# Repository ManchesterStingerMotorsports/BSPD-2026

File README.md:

# BSPD Routing Challenge - Manchester Stinger Motorsports

Welcome to the **BSPD Routing Challenge** for the Manchester Stinger Motorsports Formula Student team.

The aim of this challenge is to compare PCB layout and routing quality across the team using **the same fixed schematic and board constraints**.

You will fork this repository, route the PCB, and submit your solution via GitHub.

---

## Objective

Produce the **best-routed PCB** possible while strictly adhering to the constraints below.

This is a **layout-only challenge** - no schematic edits, no mechanical changes, no shortcuts.

---

## Deadline

**9th of February (23:59)**

---

## How to Enter

1. **Fork this repository**
2. Open the project in **KiCad** 
3. Route the PCB according to the rules below
4. Commit your changes
5. Submit your fork for review

---

## Rules (Read Carefully)

### 1. Schematic - DO NOT CHANGE
- The **schematic must remain completely unchanged**
- No component changes
- No footprint changes
- No net changes

Any schematic modification will result in **disqualification**.

---

### 2. Board Outline & Connectors - FIXED
- **Board dimensions must remain unchanged**
- **Board outline must not be edited**
- **All connectors must stay in their original positions and orientations**
- Do not move connectors even slightly

This ensures all layouts are directly comparable.

---

### 3. What You ARE Allowed to Change
- Component placement (except connectors)
- Track routing
- Via count and placement
- Copper pours / zones
- Layer usage
- Trace widths (within design rules)
- Decoupling capacitor placement (if already present in the schematic)

---

### 4. What You Are NOT Allowed to Do
- Modify the schematic in any way
- Add or remove components
- Change connector positions
- Change board size or shape
- Change footprints

---

## Judging Criteria

Layouts will be judged on:

- Signal integrity
- Routing quality
- Layer usage efficiency
- EMI considerations
- Manufacturability/Solderability
- Overall cleanliness and readability

Bonus points for:
- Thoughtful via usage
- Clear functional grouping
- Good silkscreen labelling (feel free to add cool graphics!!)

---

## Submission Guidelines

- Commit **only PCB layout changes**
- Final submission must build cleanly with **no DRC errors**
- Do not squash or rewrite history after submission
- When you are happy with your submission send me (Jame) a message.

---

## Point of Contact

The point of contact for this challenge is **me** (James Platt).

That said, please **ask questions and discuss openly in the `#st-electronics` Slack channel** wherever possible so everyone benefits.

---

## Notes

This challenge is intended to:
- Improve PCB routing skills across the team
- Encourage discussion around best practice
- Foster healthy competition within the sparky subteams

Best of luck!!

Jame ⚡

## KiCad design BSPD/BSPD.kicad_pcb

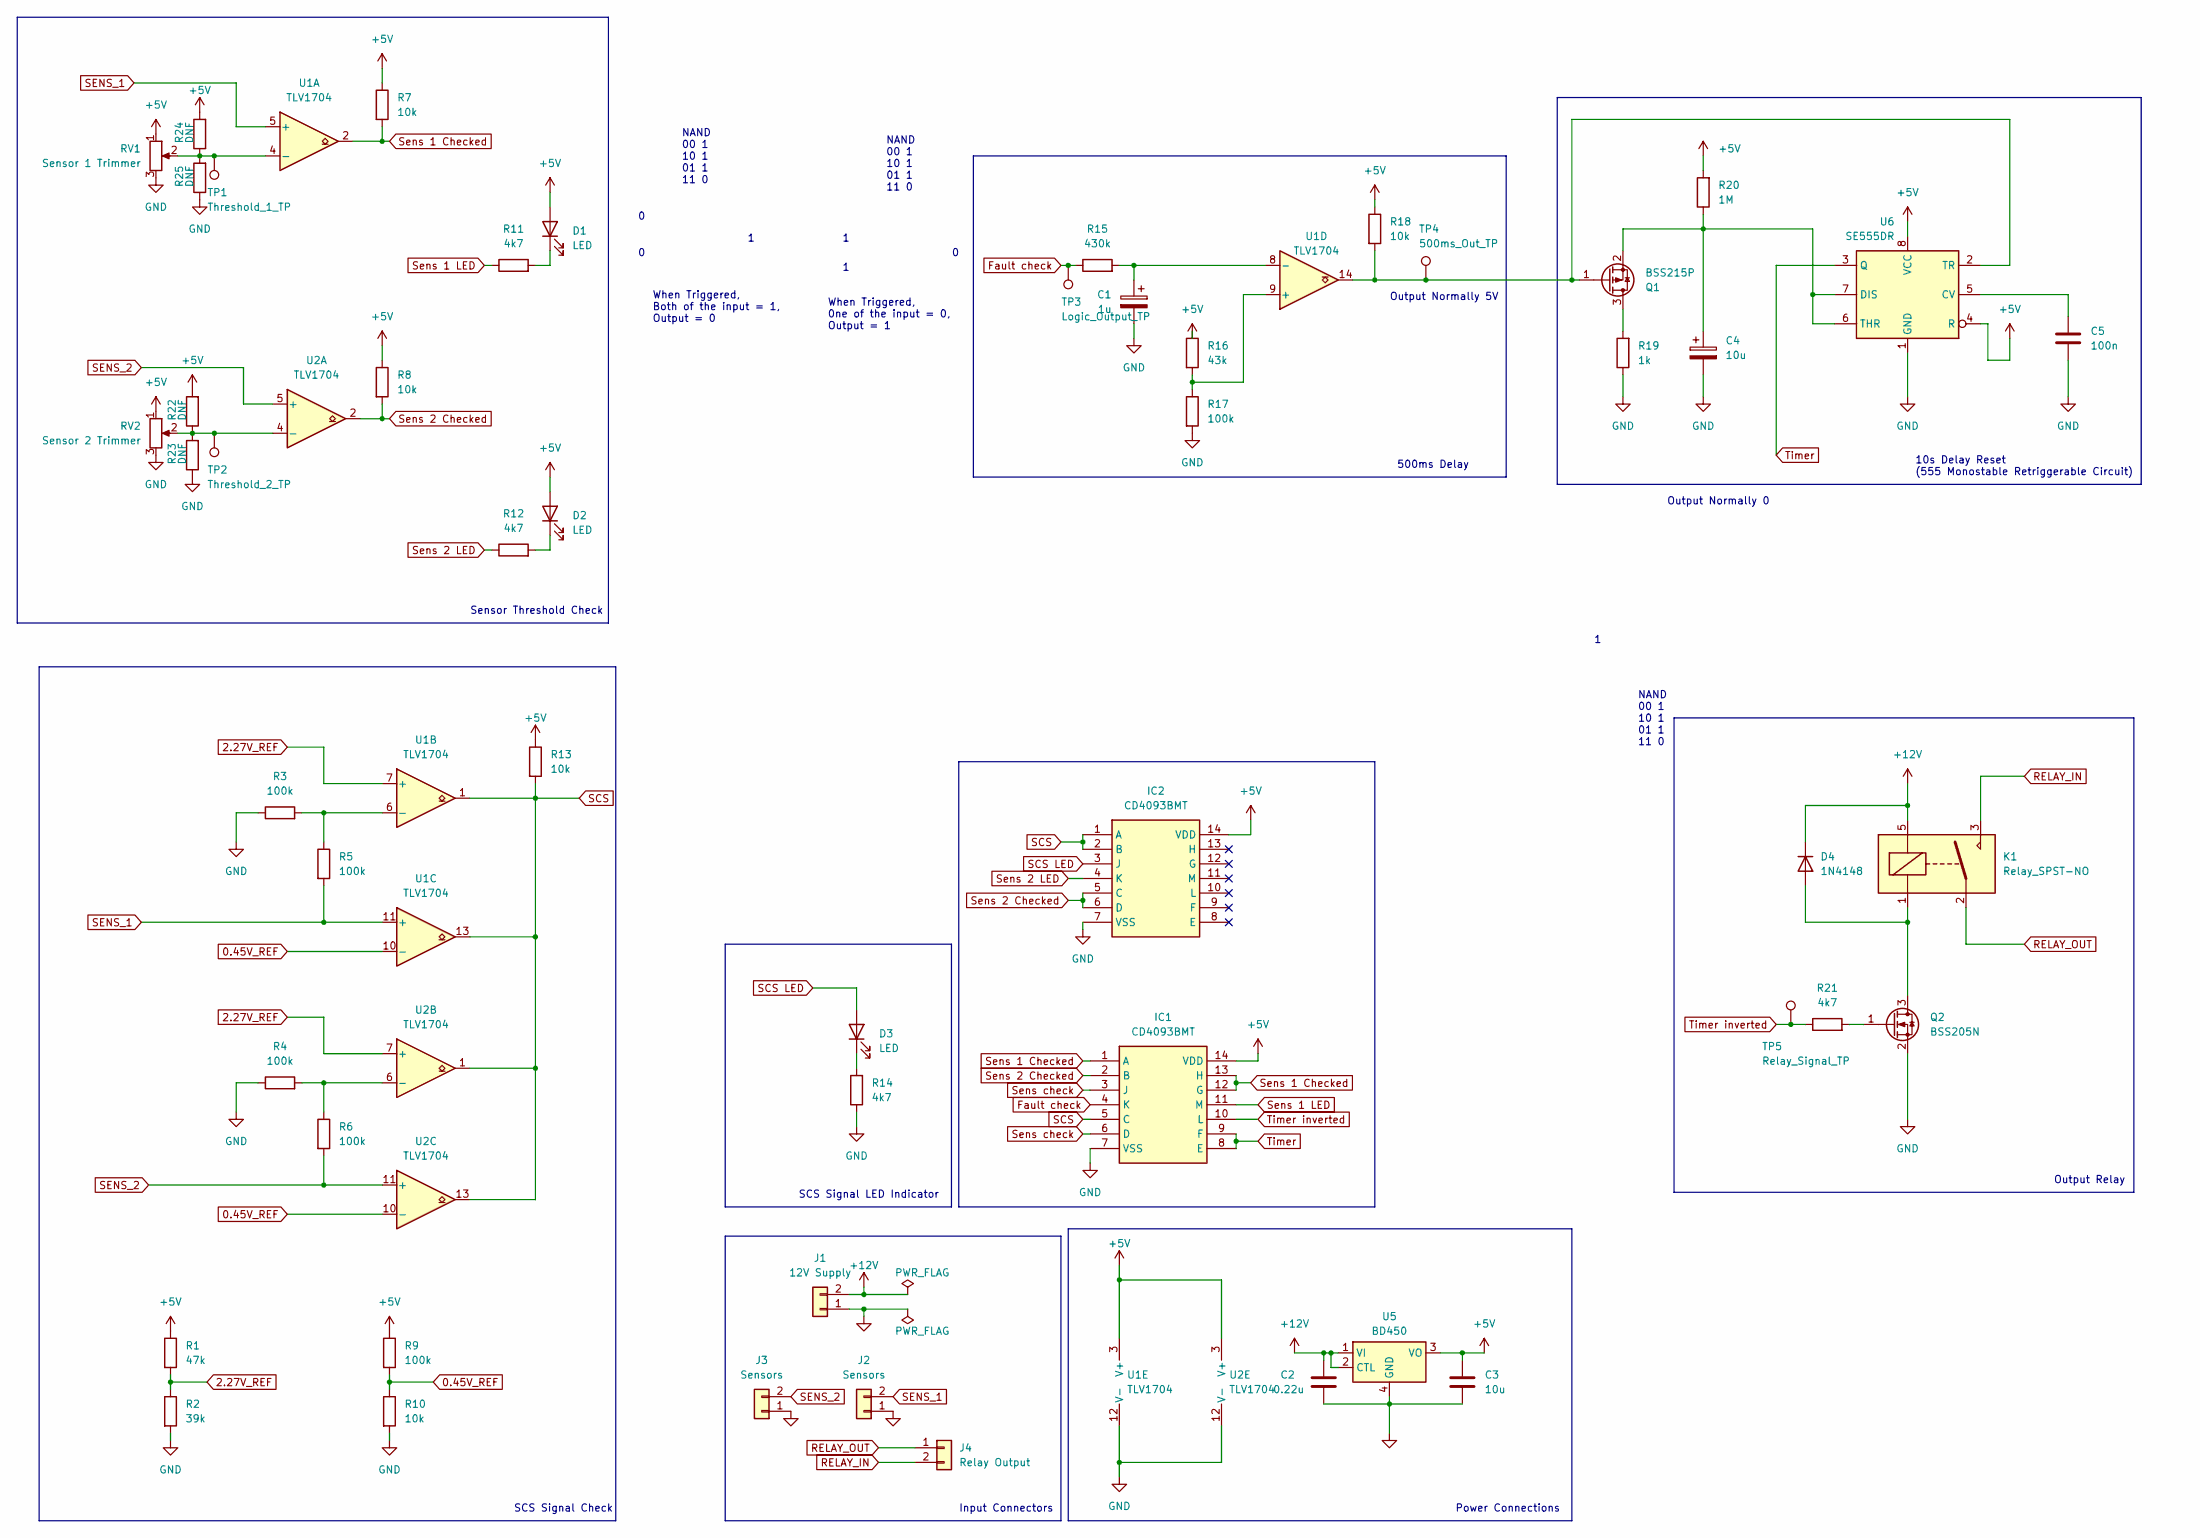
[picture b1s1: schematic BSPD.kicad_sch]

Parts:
C1: 1u; C_0603_1608Metric
C2: 0.22u; C_0603_1608Metric
C3, C4: 10u; C_0603_1608Metric
C5: 100n; C_0603_1608Metric
D1, D2, D3: LED; LED_0603_1608Metric
D4: 1N4148; SOD-123_VISHAY
IC1, IC2: CD4093BMT; Cd4093b; Manufacturer_Part_Number CD4093BMT; Mouser Part Number 595-CD4093BMT
J1: 12V Supply; JST_XA_S02B-XASK-1_1x02_P2.50mm_Horizontal
J2, J3: Sensors; JST_XA_S02B-XASK-1_1x02_P2.50mm_Horizontal
J4: Relay Output; JST_XA_S02B-XASK-1_1x02_P2.50mm_Horizontal
K1: Relay_SPST-NO; RELAY_G6RN-1_OMR
Q1: BSS215P; MOSFET_Single_SOT-23
Q2: BSS205N; MOSFET_Single_SOT-23
R1: 47k; R_0603_1608Metric
R2: 39k; R_0603_1608Metric
R3, R4, R5, R6, R9, R17: 100k; R_0603_1608Metric
R7, R8, R10, R13, R18: 10k; R_0603_1608Metric
R11, R12, R14, R21: 4k7; R_0603_1608Metric
R15: 430k; R_0603_1608Metric
R16: 43k; R_0603_1608Metric
R19: 1k; R_0603_1608Metric
R20: 1M; R_0603_1608Metric
R22, R23, R24, R25: DNF; R_0603_1608Metric
RV1: Sensor 1 Trimmer; Bourns_3314G-1
RV2: Sensor 2 Trimmer; Bourns_3314G-1
TP1: Threshold_1_TP; TestPoint_Pad_2.0x2.0mm
TP2: Threshold_2_TP; TestPoint_Pad_2.0x2.0mm
TP3: Logic_Output_TP; TestPoint_Pad_2.0x2.0mm
TP4: 500ms_Out_TP; TestPoint_Pad_2.0x2.0mm
TP5: Relay_Signal_TP; TestPoint_Pad_2.0x2.0mm
U1, U2: TLV1704; PW14_TEX
U5: BD450; Regulator_Linear_SOT-223-4
U6: SE555DR; D8

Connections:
0.45V_REF: R9.2, R10.1, U1.10 (-), U2.10 (-)
2.27V_REF: R1.2, R2.1, U1.7 (+), U2.7 (+)
+5V: C3.1, D1.2 (A), D2.2 (A), IC1.14 (VDD), IC2.14 (VDD), R1.1, R7.1, R8.1, R9.1, R13.1, R16.1, R18.1, R20.2, R22.2, R24.2, RV1.1, RV2.1, U1.3 (V+), U2.3 (V+), U5.3 (VO), U6.4 (R), U6.8 (VCC)
+12V: C2.1, D4.1 (K), J1.2, K1.5, U5.1 (VI), U5.2 (CTL)
Fault check: IC1.4 (K), R15.1, TP3.1 (1_1)
GND: C1.2, C2.2, C3.2, C4.2, C5.2, IC1.7 (VSS), IC2.7 (VSS), J1.1, J2.1, J3.1, Q2.2 (S), R2.2, R3.1, R4.1, R10.2, R14.1, R17.2, R19.1, R23.1, R25.1, RV1.3, RV2.3, U1.12 (V-), U2.12 (V-), U5.4 (GND), U6.1 (GND)
unnamed: D1.1 (K), R11.2
unnamed: D2.1 (K), R12.2
unnamed: D3.1 (K), R14.2
unnamed: D4.2 (A), K1.1, Q2.3 (D)
unnamed: Q1.3 (D), R19.2
unnamed: Q1.1 (G), R18.2, TP4.1 (1_1), U1.14, U6.2 (TR)
unnamed: C4.1, Q1.2 (S), R20.1, U6.6 (THR), U6.7 (DIS)
unnamed: Q2.1 (G), R21.2
unnamed: R24.1, R25.2, RV1.2, TP1.1 (1_1), U1.4 (-)
unnamed: R3.2, R5.1, U1.6 (-)
unnamed: R16.2, R17.1, U1.9 (+)
unnamed: C1.1, R15.2, U1.8 (-)
unnamed: R22.1, R23.2, RV2.2, TP2.1 (1_1), U2.4 (-)
unnamed: R4.2, R6.1, U2.6 (-)
unnamed: C5.1, U6.5 (CV)
RELAY_IN: J4.2, K1.3
RELAY_OUT: J4.1, K1.2
SCS: IC1.5 (C), IC2.1 (A), IC2.2 (B), R13.2, U1.1, U1.13, U2.1, U2.13
SCS LED: D3.2 (A), IC2.3 (J)
SENS_1: J2.2, R5.2, U1.5 (+), U1.11 (+)
SENS_2: J3.2, R6.2, U2.5 (+), U2.11 (+)
Sens 1 Checked: IC1.1 (A), IC1.12 (G), IC1.13 (H), R7.2, U1.2
Sens 1 LED: IC1.11 (M), R11.1
Sens 2 Checked: IC1.2 (B), IC2.5 (C), IC2.6 (D), R8.2, U2.2
Sens 2 LED: IC2.4 (K), R12.1
Sens check: IC1.3 (J), IC1.6 (D)
Timer: IC1.8 (E), IC1.9 (F), U6.3 (Q)
Timer inverted: IC1.10 (L), R21.1, TP5.1 (1_1)

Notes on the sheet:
SCS Signal Check
When Triggered, Both of the input = 1, Output = 0
500ms Delay
Output Relay
SCS Signal LED Indicator
Power Connections
NAND 00 1 10 1 01 1 11 0
Sensor Threshold Check
Output Normally 5V
Input Connectors
When Triggered, 0ne of the input = 0, Output = 1
10s Delay Reset (555 Monostable Retriggerable Circuit)
Output Normally 0

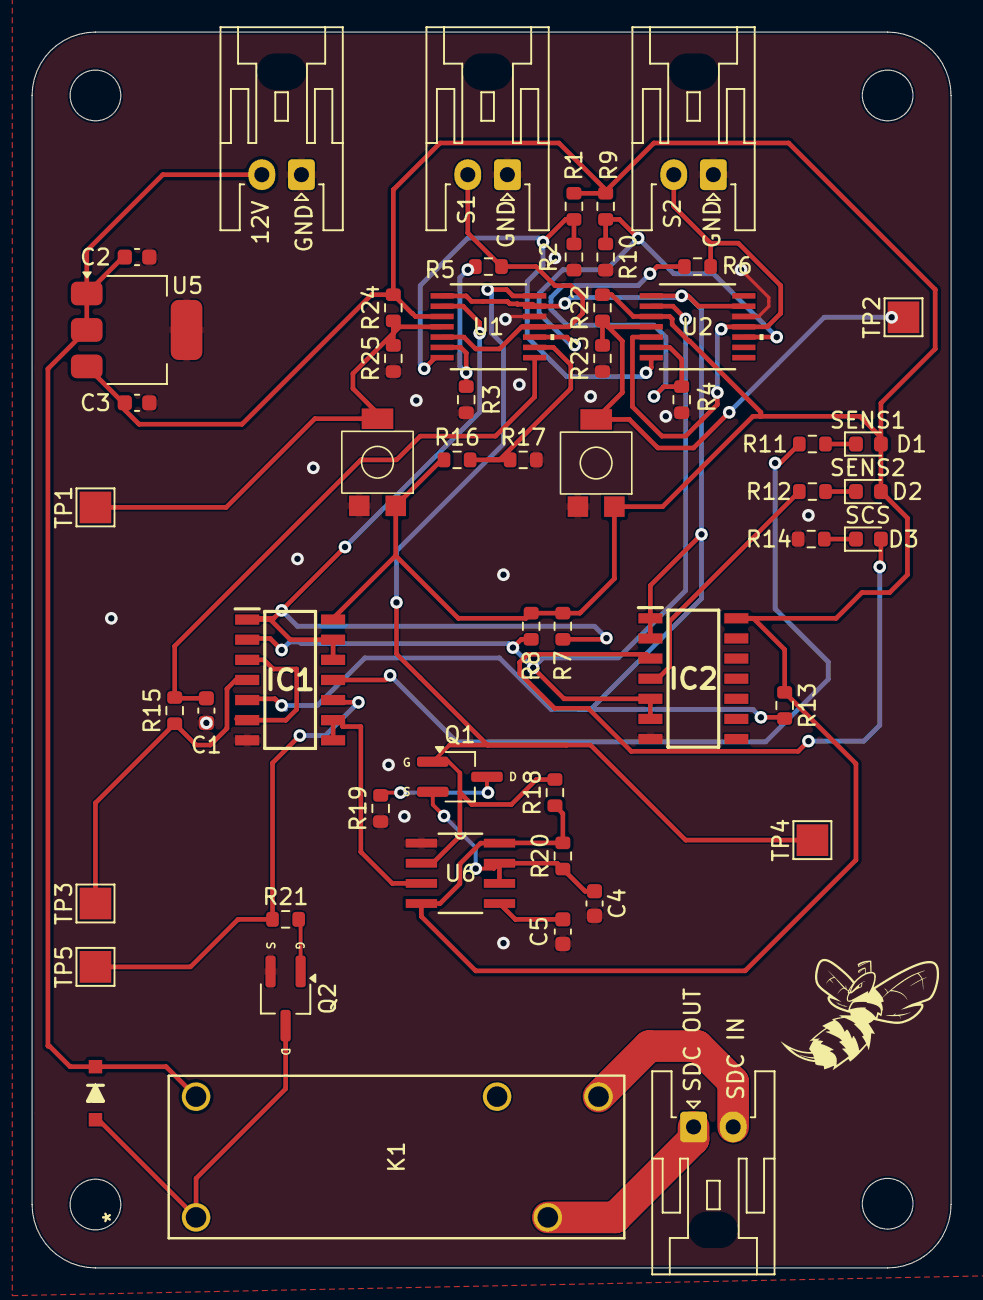
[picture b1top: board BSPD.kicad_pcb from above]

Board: 2 copper layers, 58.0 x 78.0 mm, 54 parts (0 on the bottom side), 34 nets.

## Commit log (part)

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2025-12-12 Update README with chalenge details
2026-02-10 Current Schem and defined board layout
2026-02-10 Update
    Changed outdated footprints to standard ones
2026-02-10 Finalised Schematic
2026-02-11 "Ready to buy"
2026-05-07 Fixed The footprint and used different symbols
2026-05-11 clean
2026-05-12 Fixed diode footprint
2026-05-14 clean up
2026-06-09 ready to go
